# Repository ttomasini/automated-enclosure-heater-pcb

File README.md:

# Automated Heating System PCB for the Original Prusa Enclosure

## Introduction
This repo contains a PCB implementation of the Automated Heating System control unit for the Original Prusa Enclosure.

Find the schematics [here](doc/schematic.pdf).

## Manufacturing
Please ensure that the PCB is manufactured with 70 μm (2 oz/ft²) outer copper layer thickness.

## Credits
The original idea and the base principle of the schematic have been designed and published by Lars Knust ([@LarsKnust at Github](https://github.com/LarsKnust) / [@lars at printables.com](https://www.printables.com/@lars)).

Link to the model on Printables: https://www.printables.com/model/561491

This PCB has been proudly designed with KiCad.

## License
This repository is licensed under the GNU General Public License, Version 3. See [the LICENSE file](LICENSE) for more information.

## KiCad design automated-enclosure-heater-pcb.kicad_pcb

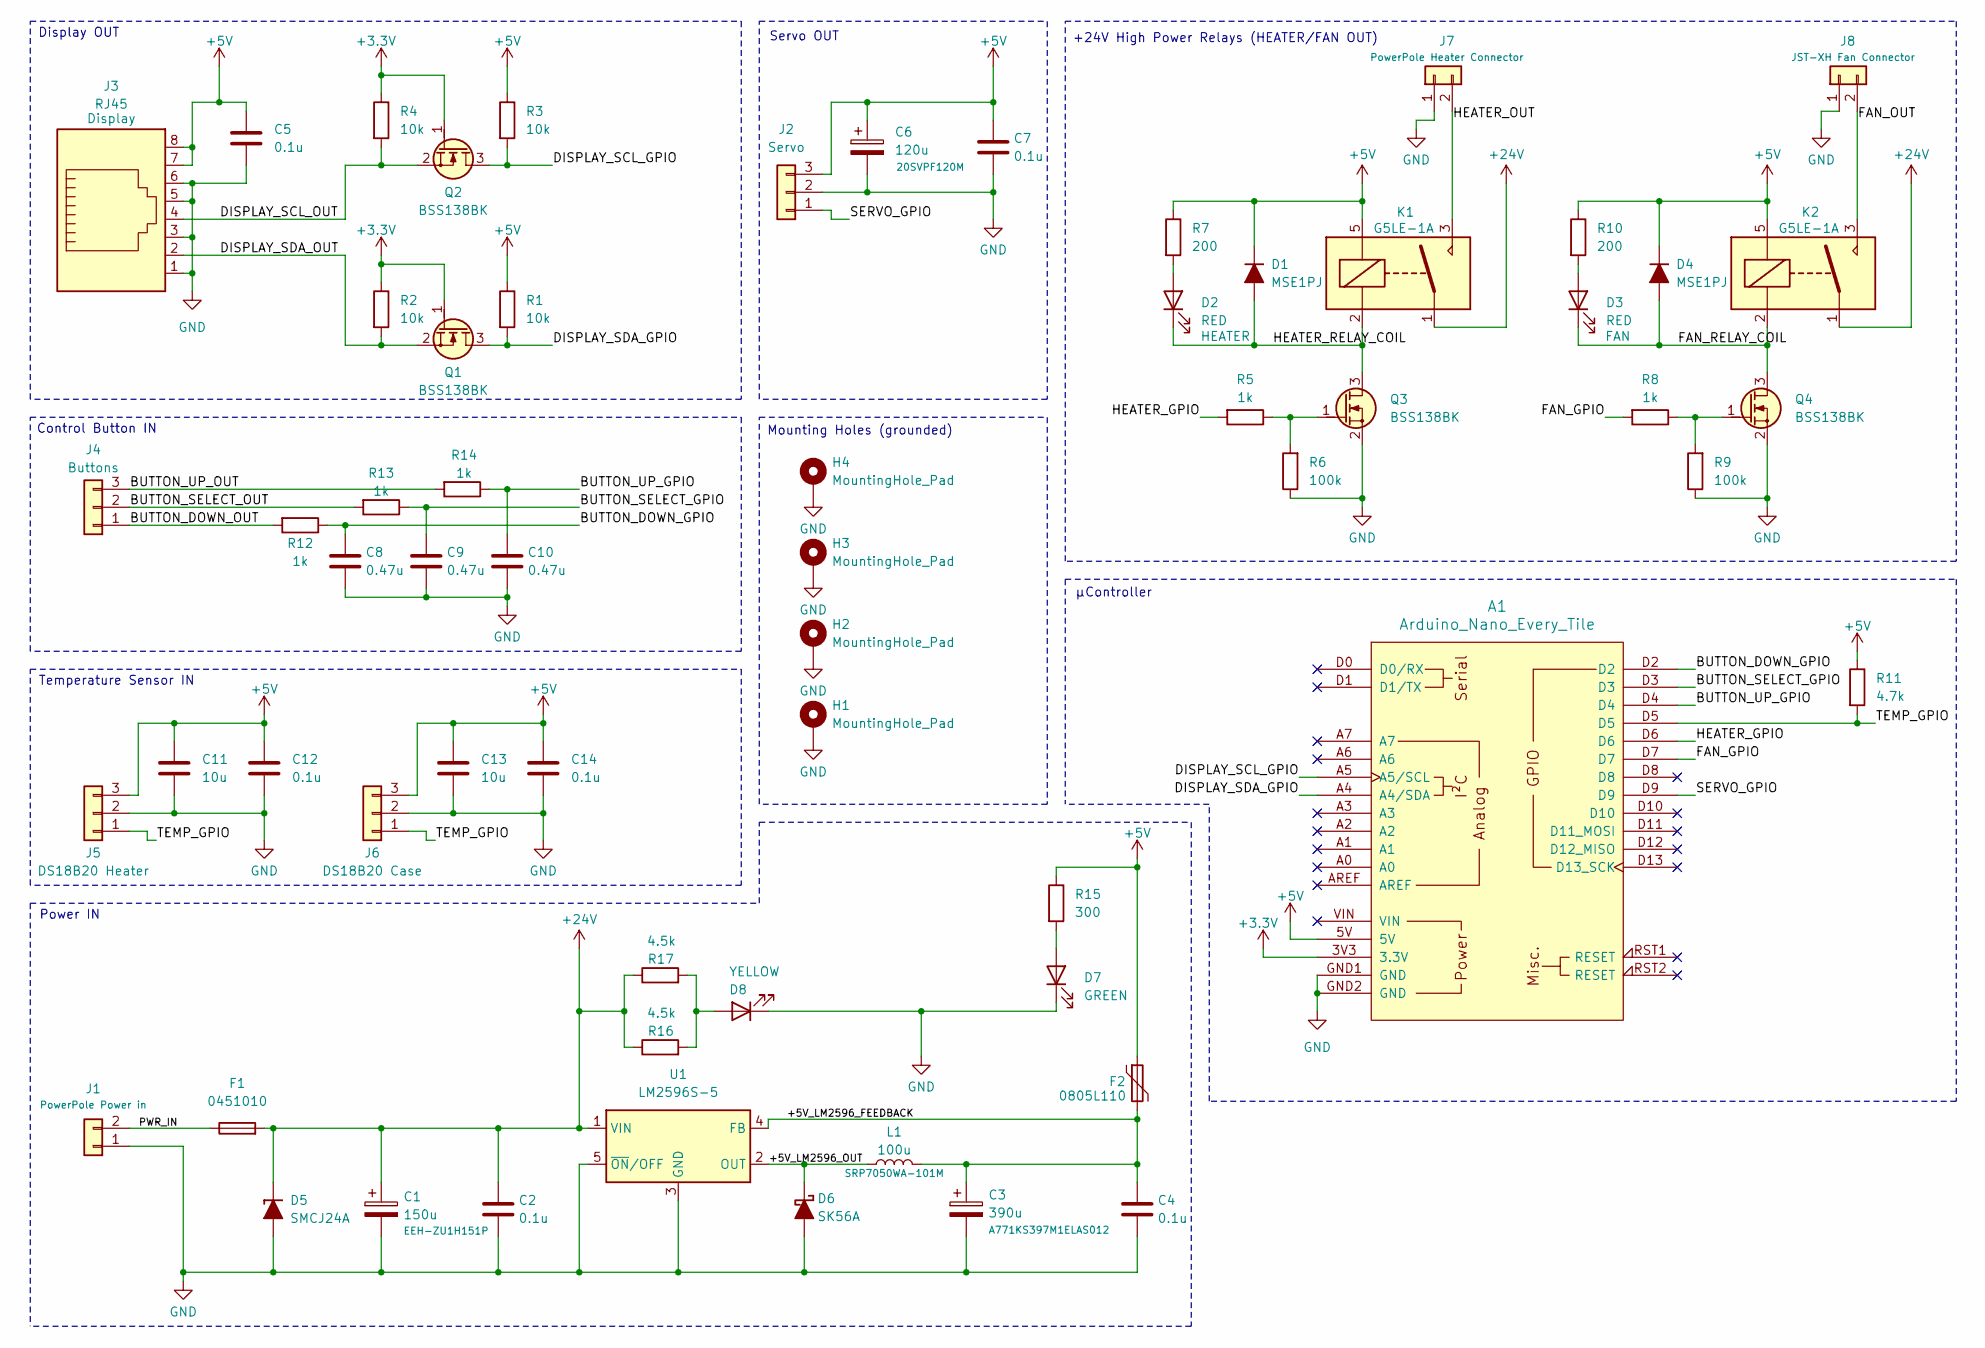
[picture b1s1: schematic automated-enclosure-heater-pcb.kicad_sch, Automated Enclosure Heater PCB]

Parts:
A1: Arduino_Nano_Every_Tile
C1: 150u; CP_Elec_10x12.6; Part Number EEH-ZU1H151P
C2, C4, C5, C7, C12, C14: 0.1u; C_0805_2012Metric
C3: 390u; CP_Elec_8x12.2_KEMET; Part Number A771KS397M1ELAS012
C6: 120u; CP_Elec_6.3x5.9; Part Number 20SVPF120M
C8, C9, C10: 0.47u; C_0805_2012Metric
C11, C13: 10u; C_0805_2012Metric
D1, D4: MSE1PJ; D_MicroSMP_AK
D2, D3: RED; LED_0805_2012Metric
D5: SMCJ24A; D_SMC
D6: SK56A; D_SMB
D7: GREEN; LED_0805_2012Metric
D8: YELLOW; LED_0805_2012Metric
F1: 0451010; Fuse_Littelfuse-NANO2-451_453
F2: 0805L110; Fuse_0805_2012Metric
H1, H2, H3, H4: MountingHole_Pad; MountingHole_3.2mm_M3_Pad_TopOnly
J1: PowerPole Power in; Anderson_PowerPole_25A_Right_Angle_Pair
J2: Servo; JST_PH_S3B-PH-K_1x03_P2.00mm_Horizontal
J3: RJ45; RJ45_Amphenol_54602-x08_Horizontal
J4: Buttons; JST_PH_S3B-PH-K_1x03_P2.00mm_Horizontal
J5: DS18B20 Heater; JST_PH_S3B-PH-K_1x03_P2.00mm_Horizontal
J6: DS18B20 Case; JST_PH_S3B-PH-K_1x03_P2.00mm_Horizontal
J7: PowerPole Heater Connector; Anderson_PowerPole_25A_Right_Angle_Pair
J8: JST-XH Fan Connector; JST_XH_S2B-XH-A-1_1x02_P2.50mm_Horizontal
K1, K2: G5LE-1A; Relay_SPST_NO_Omron-G5LE-1A
L1: 100u; L_Bourns_SRP7050WA_Series
Q1, Q2, Q3, Q4: BSS138BK; SOT-23
R1, R2, R3, R4: 10k; R_0805_2012Metric
R5, R8, R12, R13, R14: 1k; R_0805_2012Metric
R6, R9: 100k; R_0805_2012Metric
R7, R10: 200; R_0805_2012Metric
R11: 4.7k; R_0805_2012Metric
R15: 300; R_0805_2012Metric
R16, R17: 4.5k; R_0805_2012Metric
U1: LM2596S-5; TO-263-5_TabPin3

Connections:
+3.3V: A1.3V3 (3.3V), Q1.1 (G), Q2.1 (G), R2.1, R4.1
+5V: A1.5V, C5.1, C6.1, C7.1, C11.1, C12.1, C13.1, C14.1, D1.1 (K), D4.1 (K), F2.1, J2.3, J3.7, J3.8, J5.3, J6.3, K1.5, K2.5, R1.1, R3.1, R7.1, R10.1, R11.1, R15.1
+24V: C1.1, C2.1, D5.1 (K), F1.2, K1.1, K2.1, R16.1, R17.1, U1.1 (VIN)
/+5V_LM2596_FEEDBACK: C3.1, C4.1, F2.2, L1.2, U1.4 (FB)
/+5V_LM2596_OUT: D6.1 (K), L1.1, U1.2 (OUT)
/BUTTON_DOWN_GPIO: A1.D2, C8.1, R12.1
/BUTTON_DOWN_OUT: J4.1, R12.2
/BUTTON_SELECT_GPIO: A1.D3, C9.1, R13.1
/BUTTON_SELECT_OUT: J4.2, R13.2
/BUTTON_UP_GPIO: A1.D4, C10.1, R14.1
/BUTTON_UP_OUT: J4.3, R14.2
/DISPLAY_SCL_GPIO: A1.A5 (A5/SCL), Q2.3 (D), R3.2
/DISPLAY_SCL_OUT: J3.4, Q2.2 (S), R4.2
/DISPLAY_SDA_GPIO: A1.A4 (A4/SDA), Q1.3 (D), R1.2
/DISPLAY_SDA_OUT: J3.2, Q1.2 (S), R2.2
/FAN_GPIO: A1.D7, R8.2
/FAN_OUT: J8.2, K2.3
/FAN_RELAY_COIL: D3.1 (K), D4.2 (A), K2.2, Q4.3 (D)
/HEATER_GPIO: A1.D6, R5.2
/HEATER_OUT: J7.2, K1.3
/HEATER_RELAY_COIL: D1.2 (A), D2.1 (K), K1.2, Q3.3 (D)
/PWR_IN: F1.1, J1.2
/SERVO_GPIO: A1.D9, J2.1
/TEMP_GPIO: A1.D5, J5.1, J6.1, R11.2
GND: A1.GND1 (GND), A1.GND2 (GND), C1.2, C2.2, C3.2, C4.2, C5.2, C6.2, C7.2, C8.2, C9.2, C10.2, C11.2, C12.2, C13.2, C14.2, D5.2 (A), D6.2 (A), D7.1 (K), D8.1 (K), H1.1, H2.1, H3.1, H4.1, J1.1, J2.2, J3.1, J3.3, J3.5, J3.6, J5.2, J6.2, J7.1, J8.1, Q3.2 (S), Q4.2 (S), R6.1, R9.1, U1.3 (GND), U1.5 (~ON/OFF)
unnamed: D2.2 (A), R7.2
unnamed: D3.2 (A), R10.2
unnamed: D7.2 (A), R15.2
unnamed: D8.2 (A), R16.2, R17.2
unnamed: Q3.1 (G), R5.1, R6.2
unnamed: Q4.1 (G), R8.1, R9.2

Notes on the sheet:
Servo OUT
Power IN
Temperature Sensor IN
µController
+24V High Power Relays (HEATER/FAN OUT)
Mounting Holes (grounded)
Control Button IN
Display OUT

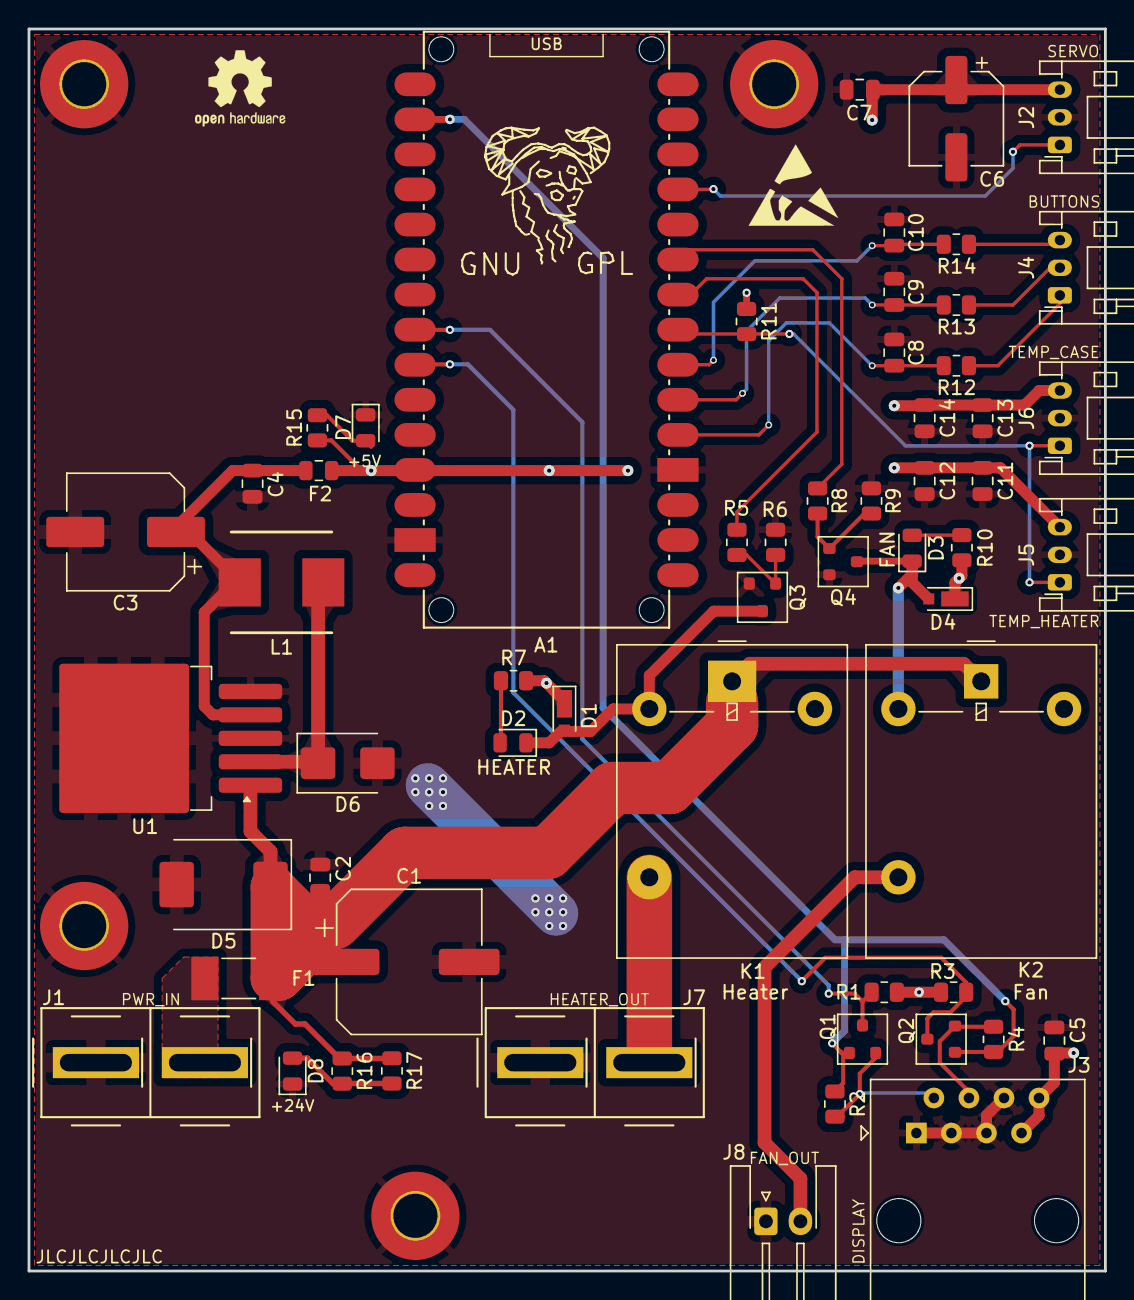
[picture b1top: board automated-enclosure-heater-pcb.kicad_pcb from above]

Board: 2 copper layers, 78.0 x 90.0 mm, 62 parts (0 on the bottom side), 31 nets.

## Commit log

2024-03-24 Add schematic and pictures to README.
2024-03-30 Add fitting 3d printed case made with freecad
2024-04-03 Fix LED issue
2024-04-03 Add minor silkscreen adjustments
2024-04-05 Fix DISP pinout
2024-04-07 Adjust Arduino pinout and push version to v0.2
2024-04-08 Add additional case lid screw holes
2024-04-08 Add second resistor for 24V LED and adjust power plane size
2024-04-14 Improve heat dissipation and lid fastening
